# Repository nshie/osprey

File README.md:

# Osprey
A unibody ergonomic ortholinear keyboard
- ergonomic wrist angle
- ortholinear columnar-stagger
- 60% layout (~ish)
- thumb clusters for modifiers and chording
- kailh hotswap sockets
- USB-C

### Features to change:
- leds in the pcb are not properly implemented with capacitors, WOULD NOT recommend building this board with the leds
- pcb uses 0805 diode pads; might have some difficulty finding them (0603 will work on the pcb)

## Important Note:
This board is very much a prototype, and I would not recommend using the files without modification.

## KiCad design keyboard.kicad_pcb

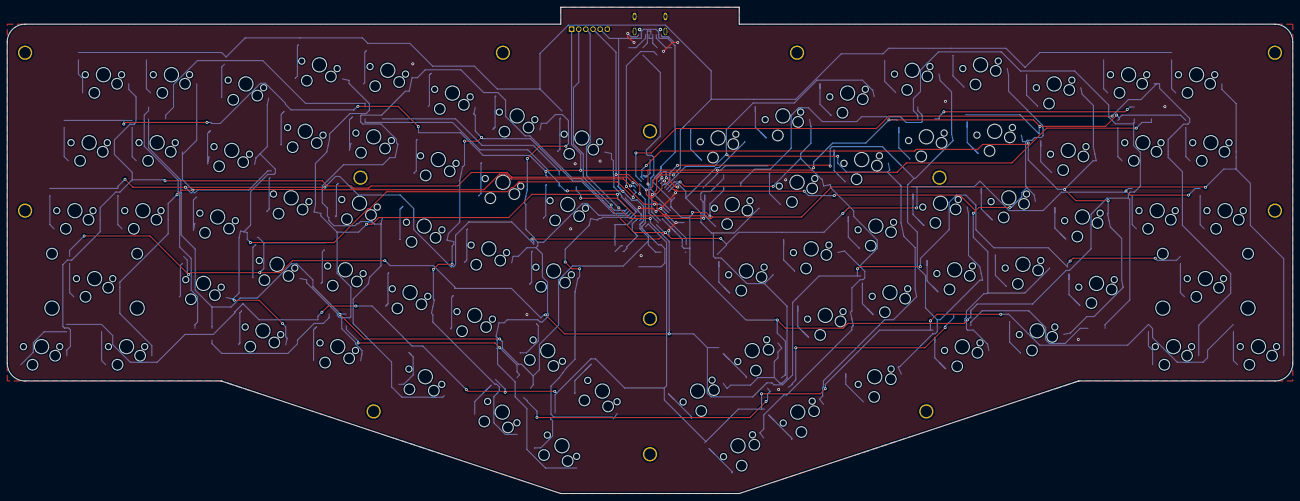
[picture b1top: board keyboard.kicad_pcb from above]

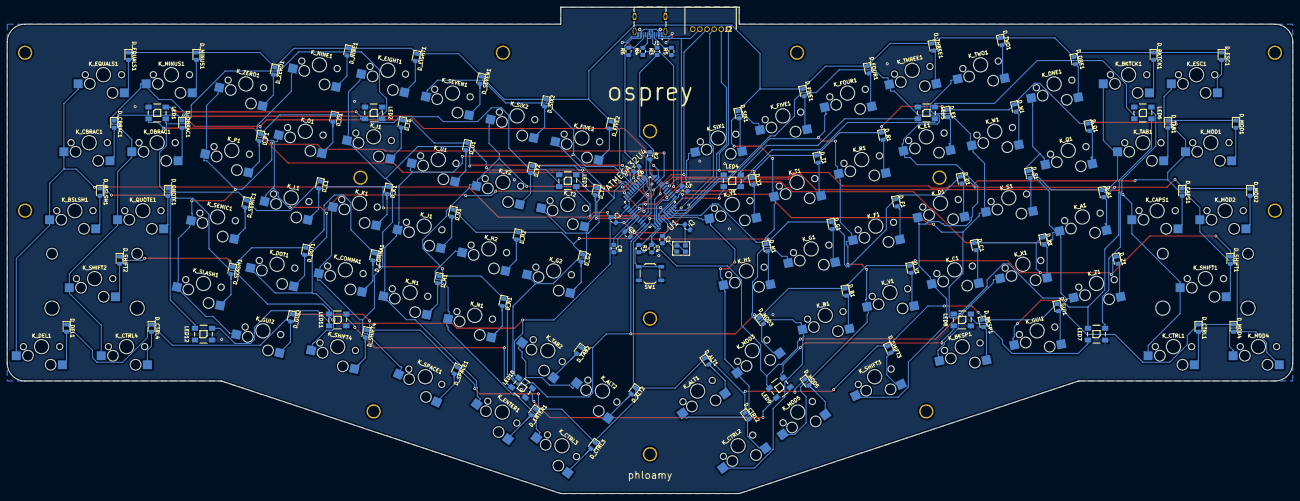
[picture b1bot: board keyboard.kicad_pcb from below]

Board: 2 copper layers, 360.2 x 136.3 mm, 200 parts (109 on the bottom side), 124 nets.

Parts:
C1, C2: 22p; C_0805_2012Metric_Pad1.15x1.40mm_HandSolder
C3, C4, C5, C6: 0.1u; C_0805_2012Metric_Pad1.15x1.40mm_HandSolder
C7: 4.7u; C_0805_2012Metric_Pad1.15x1.40mm_HandSolder
C8: 1u; C_0805_2012Metric_Pad1.15x1.40mm_HandSolder
D_A1: D; D_0805_2012Metric_Pad1.15x1.40mm_HandSolder
D_ALT1, D_ALT2: D; D_0805_2012Metric_Pad1.15x1.40mm_HandSolder
D_B1: D; D_0805_2012Metric_Pad1.15x1.40mm_HandSolder
D_BKSP1: D; D_0805_2012Metric_Pad1.15x1.40mm_HandSolder
D_BKTCK1: D; D_0805_2012Metric_Pad1.15x1.40mm_HandSolder
D_BSLSH1: D; D_0805_2012Metric_Pad1.15x1.40mm_HandSolder
D_C1: D; D_0805_2012Metric_Pad1.15x1.40mm_HandSolder
D_CAPS1: D; D_0805_2012Metric_Pad1.15x1.40mm_HandSolder
D_CBRAC1: D; D_0805_2012Metric_Pad1.15x1.40mm_HandSolder
D_COMMA1: D; D_0805_2012Metric_Pad1.15x1.40mm_HandSolder
D_CTRL1, D_CTRL2, D_CTRL3, D_CTRL4: D; D_0805_2012Metric_Pad1.15x1.40mm_HandSolder
D_D1: D; D_0805_2012Metric_Pad1.15x1.40mm_HandSolder
D_DEL1: D; D_0805_2012Metric_Pad1.15x1.40mm_HandSolder
D_DOT1: D; D_0805_2012Metric_Pad1.15x1.40mm_HandSolder
D_E1: D; D_0805_2012Metric_Pad1.15x1.40mm_HandSolder
D_EIGHT1: D; D_0805_2012Metric_Pad1.15x1.40mm_HandSolder
D_ENTER1: D; D_0805_2012Metric_Pad1.15x1.40mm_HandSolder
D_EQUALS1: D; D_0805_2012Metric_Pad1.15x1.40mm_HandSolder
D_ESC1: D; D_0805_2012Metric_Pad1.15x1.40mm_HandSolder
D_F1: D; D_0805_2012Metric_Pad1.15x1.40mm_HandSolder
D_FIVE1, D_FIVE2: D; D_0805_2012Metric_Pad1.15x1.40mm_HandSolder
D_FOUR1: D; D_0805_2012Metric_Pad1.15x1.40mm_HandSolder
D_G1, D_G2: D; D_0805_2012Metric_Pad1.15x1.40mm_HandSolder
D_GUI1, D_GUI2: D; D_0805_2012Metric_Pad1.15x1.40mm_HandSolder
D_H1, D_H2: D; D_0805_2012Metric_Pad1.15x1.40mm_HandSolder
D_I1: D; D_0805_2012Metric_Pad1.15x1.40mm_HandSolder
D_J1: D; D_0805_2012Metric_Pad1.15x1.40mm_HandSolder
D_K1: D; D_0805_2012Metric_Pad1.15x1.40mm_HandSolder
D_L1: D; D_0805_2012Metric_Pad1.15x1.40mm_HandSolder
D_M1: D; D_0805_2012Metric_Pad1.15x1.40mm_HandSolder
D_MINUS1: D; D_0805_2012Metric_Pad1.15x1.40mm_HandSolder
D_MOD1, D_MOD2, D_MOD3, D_MOD4, D_MOD5: D; D_0805_2012Metric_Pad1.15x1.40mm_HandSolder
D_N1: D; D_0805_2012Metric_Pad1.15x1.40mm_HandSolder
D_NINE1: D; D_0805_2012Metric_Pad1.15x1.40mm_HandSolder
D_O1: D; D_0805_2012Metric_Pad1.15x1.40mm_HandSolder
D_OBRAC1: D; D_0805_2012Metric_Pad1.15x1.40mm_HandSolder
D_ONE1: D; D_0805_2012Metric_Pad1.15x1.40mm_HandSolder
D_P1: D; D_0805_2012Metric_Pad1.15x1.40mm_HandSolder
D_Q1: D; D_0805_2012Metric_Pad1.15x1.40mm_HandSolder
D_QUOTE1: D; D_0805_2012Metric_Pad1.15x1.40mm_HandSolder
D_R1: D; D_0805_2012Metric_Pad1.15x1.40mm_HandSolder
D_S1: D; D_0805_2012Metric_Pad1.15x1.40mm_HandSolder
D_SEMIC1: D; D_0805_2012Metric_Pad1.15x1.40mm_HandSolder
D_SEVEN1: D; D_0805_2012Metric_Pad1.15x1.40mm_HandSolder
D_SHIFT1, D_SHIFT2, D_SHIFT3, D_SHIFT4: D; D_0805_2012Metric_Pad1.15x1.40mm_HandSolder
D_SIX1, D_SIX2: D; D_0805_2012Metric_Pad1.15x1.40mm_HandSolder
D_SLASH1: D; D_0805_2012Metric_Pad1.15x1.40mm_HandSolder
D_SPACE1: D; D_0805_2012Metric_Pad1.15x1.40mm_HandSolder
D_T1, D_T2: D; D_0805_2012Metric_Pad1.15x1.40mm_HandSolder
D_TAB1, D_TAB2: D; D_0805_2012Metric_Pad1.15x1.40mm_HandSolder
D_THREE1: D; D_0805_2012Metric_Pad1.15x1.40mm_HandSolder
D_TWO1: D; D_0805_2012Metric_Pad1.15x1.40mm_HandSolder
D_U1: D; D_0805_2012Metric_Pad1.15x1.40mm_HandSolder
D_V1: D; D_0805_2012Metric_Pad1.15x1.40mm_HandSolder
D_W1: D; D_0805_2012Metric_Pad1.15x1.40mm_HandSolder
D_X1: D; D_0805_2012Metric_Pad1.15x1.40mm_HandSolder
D_Y1, D_Y2: D; D_0805_2012Metric_Pad1.15x1.40mm_HandSolder
D_Z1: D; D_0805_2012Metric_Pad1.15x1.40mm_HandSolder
D_ZERO1: D; D_0805_2012Metric_Pad1.15x1.40mm_HandSolder
HOLE1, HOLE2, HOLE3, HOLE4, HOLE5, HOLE6, HOLE7, HOLE8, HOLE9, HOLE10, HOLE11, HOLE12, HOLE13: HOLE_M3
J1: TYPE-C-31-M-12; HRO_TYPE-C-31-M-12
J2: DF3A-6P-2DS; SHDRRA6W60P0X200_1X6_1400X720X530P
K_A1: KEYSW; MXOnly-1U-Hotswap
K_ALT1, K_ALT2: KEYSW; MXOnly-1U-Hotswap
K_B1: KEYSW; MXOnly-1U-Hotswap
K_BKSP1: KEYSW; MXOnly-1.25U-Hotswap
K_BKTCK1: KEYSW; MXOnly-1U-Hotswap
K_BSLSH1: KEYSW; MXOnly-1U-Hotswap
K_C1: KEYSW; MXOnly-1U-Hotswap
K_CAPS1: KEYSW; MXOnly-1U-Hotswap
K_CBRAC1: KEYSW; MXOnly-1U-Hotswap
K_COMMA1: KEYSW; MXOnly-1U-Hotswap
K_CTRL1, K_CTRL4: KEYSW; MXOnly-1.5U-Hotswap
K_CTRL2, K_CTRL3: KEYSW; MXOnly-1U-Hotswap
K_D1: KEYSW; MXOnly-1U-Hotswap
K_DEL1: KEYSW; MXOnly-1U-Hotswap
K_DOT1: KEYSW; MXOnly-1U-Hotswap
K_E1: KEYSW; MXOnly-1U-Hotswap
K_EIGHT1: KEYSW; MXOnly-1U-Hotswap
K_ENTER1: KEYSW; MXOnly-1U-Hotswap
K_EQUALS1: KEYSW; MXOnly-1U-Hotswap
K_ESC1: KEYSW; MXOnly-1U-Hotswap
K_F1: KEYSW; MXOnly-1U-Hotswap
K_FIVE1, K_FIVE2: KEYSW; MXOnly-1U-Hotswap
K_FOUR1: KEYSW; MXOnly-1U-Hotswap
K_G1, K_G2: KEYSW; MXOnly-1U-Hotswap
K_GUI1, K_GUI2: KEYSW; MXOnly-1U-Hotswap
K_H1, K_H2: KEYSW; MXOnly-1U-Hotswap
K_I1: KEYSW; MXOnly-1U-Hotswap
K_J1: KEYSW; MXOnly-1U-Hotswap
K_K1: KEYSW; MXOnly-1U-Hotswap
K_L1: KEYSW; MXOnly-1U-Hotswap
K_M1: KEYSW; MXOnly-1U-Hotswap
K_MINUS1: KEYSW; MXOnly-1U-Hotswap
K_MOD1, K_MOD2, K_MOD3, K_MOD4, K_MOD5: KEYSW; MXOnly-1U-Hotswap
K_N1: KEYSW; MXOnly-1U-Hotswap
K_NINE1: KEYSW; MXOnly-1U-Hotswap
K_O1: KEYSW; MXOnly-1U-Hotswap
K_OBRAC1: KEYSW; MXOnly-1U-Hotswap
K_ONE1: KEYSW; MXOnly-1U-Hotswap
K_P1: KEYSW; MXOnly-1U-Hotswap
K_Q1: KEYSW; MXOnly-1U-Hotswap
K_QUOTE1: KEYSW; MXOnly-1U-Hotswap
K_R1: KEYSW; MXOnly-1U-Hotswap
K_S1: KEYSW; MXOnly-1U-Hotswap
K_SEMIC1: KEYSW; MXOnly-1U-Hotswap
K_SEVEN1: KEYSW; MXOnly-1U-Hotswap
K_SHIFT1, K_SHIFT2: KEYSW; MXOnly-2U-Hotswap-ReversedStabilizers
K_SHIFT3, K_SHIFT4: KEYSW; MXOnly-1.25U-Hotswap
K_SIX1, K_SIX2: KEYSW; MXOnly-1U-Hotswap
K_SLASH1: KEYSW; MXOnly-1U-Hotswap
K_SPACE1: KEYSW; MXOnly-1.25U-Hotswap
K_T1, K_T2: KEYSW; MXOnly-1U-Hotswap
K_TAB1, K_TAB2: KEYSW; MXOnly-1U-Hotswap
K_THREE1: KEYSW; MXOnly-1U-Hotswap
K_TWO1: KEYSW; MXOnly-1U-Hotswap
K_U1: KEYSW; MXOnly-1U-Hotswap
K_V1: KEYSW; MXOnly-1U-Hotswap
K_W1: KEYSW; MXOnly-1U-Hotswap
K_X1: KEYSW; MXOnly-1U-Hotswap
K_Y1, K_Y2: KEYSW; MXOnly-1U-Hotswap
K_Z1: KEYSW; MXOnly-1U-Hotswap
K_ZERO1: KEYSW; MXOnly-1U-Hotswap
LED1, LED2, LED3, LED4, LED5, LED6, LED7, LED8, LED9, LED10, LED11, LED12: WS2812B
R1, R2: 10k; R_0805_2012Metric_Pad1.15x1.40mm_HandSolder
R3, R4: 22; R_0805_2012Metric_Pad1.15x1.40mm_HandSolder
R5, R6: 5.1k; R_0805_2012Metric_Pad1.15x1.40mm_HandSolder
SW1: SW_PUSH; SW_SPST_TL3342
U1: ATMEGA32U4; ATmega32U4
X1: XTAL_GND; FA-238

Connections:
GND: C1.2, C2.2, C3.2, C4.2, C5.2, C6.2, C7.2, C8.2, J1.A1B12, J1.B1A12, J1.S1, J1.S2, J1.S3, J1.S4, J2.6, LED1.3, LED2.3, LED3.3, LED4.3, LED5.3, LED6.3, LED7.3, LED8.3, LED9.3, LED10.3, LED11.3, LED12.3, R2.1, R5.1, R6.1, SW1.1, U1.5, U1.15, U1.23, U1.35, U1.43, X1.3
unnamed: C1.1, U1.16, X1.1
unnamed: C2.1, U1.17, X1.2
unnamed: C8.1, U1.6
unnamed: D_A1.2, K_A1.2
unnamed: D_ALT1.2, K_ALT1.2
unnamed: D_ALT2.2, K_ALT2.2
unnamed: D_B1.2, K_B1.2
unnamed: D_BKSP1.2, K_BKSP1.2
unnamed: D_BKTCK1.2, K_BKTCK1.2
unnamed: D_BSLSH1.2, K_BSLSH1.2
unnamed: D_C1.2, K_C1.2
unnamed: D_CAPS1.2, K_CAPS1.2
unnamed: D_CBRAC1.2, K_CBRAC1.2
unnamed: D_COMMA1.2, K_COMMA1.2
unnamed: D_CTRL1.2, K_CTRL1.2
unnamed: D_CTRL2.2, K_CTRL2.2
unnamed: D_CTRL3.2, K_CTRL3.2
unnamed: D_CTRL4.2, K_CTRL4.2
unnamed: D_D1.2, K_D1.2
unnamed: D_DEL1.2, K_DEL1.2
unnamed: D_DOT1.2, K_DOT1.2
unnamed: D_E1.2, K_E1.2
unnamed: D_EIGHT1.2, K_EIGHT1.2
unnamed: D_ENTER1.2, K_ENTER1.2
unnamed: D_EQUALS1.2, K_EQUALS1.2
unnamed: D_ESC1.2, K_ESC1.2
unnamed: D_F1.2, K_F1.2
unnamed: D_FIVE1.2, K_FIVE1.2
unnamed: D_FIVE2.2, K_FIVE2.2
unnamed: D_FOUR1.2, K_FOUR1.2
unnamed: D_G1.2, K_G1.2
unnamed: D_G2.2, K_G2.2
unnamed: D_GUI1.2, K_GUI1.2
unnamed: D_GUI2.2, K_GUI2.2
unnamed: D_H1.2, K_H1.2
unnamed: D_H2.2, K_H2.2
unnamed: D_I1.2, K_I1.2
unnamed: D_J1.2, K_J1.2
unnamed: D_K1.2, K_K1.2
unnamed: D_L1.2, K_L1.2
unnamed: D_M1.2, K_M1.2
unnamed: D_MINUS1.2, K_MINUS1.2
unnamed: D_MOD1.2, K_MOD1.2
unnamed: D_MOD2.2, K_MOD2.2
unnamed: D_MOD3.2, K_MOD3.2
unnamed: D_MOD4.2, K_MOD4.2
unnamed: D_MOD5.2, K_MOD5.2
unnamed: D_N1.2, K_N1.2
unnamed: D_NINE1.2, K_NINE1.2
unnamed: D_O1.2, K_O1.2
unnamed: D_OBRAC1.2, K_OBRAC1.2
unnamed: D_ONE1.2, K_ONE1.2
unnamed: D_P1.2, K_P1.2
unnamed: D_Q1.2, K_Q1.2
unnamed: D_QUOTE1.2, K_QUOTE1.2
unnamed: D_R1.2, K_R1.2
unnamed: D_S1.2, K_S1.2
unnamed: D_SEMIC1.2, K_SEMIC1.2
unnamed: D_SEVEN1.2, K_SEVEN1.2
unnamed: D_SHIFT1.2, K_SHIFT1.2
unnamed: D_SHIFT2.2, K_SHIFT2.2
unnamed: D_SHIFT3.2, K_SHIFT3.2
unnamed: D_SHIFT4.2, K_SHIFT4.2
unnamed: D_SIX1.2, K_SIX1.2
unnamed: D_SIX2.2, K_SIX2.2
unnamed: D_SLASH1.2, K_SLASH1.2
unnamed: D_SPACE1.2, K_SPACE1.2
unnamed: D_T1.2, K_T1.2
unnamed: D_T2.2, K_T2.2
unnamed: D_TAB1.2, K_TAB1.2
unnamed: D_TAB2.2, K_TAB2.2
unnamed: D_THREE1.2, K_THREE1.2
unnamed: D_TWO1.2, K_TWO1.2
unnamed: D_U1.2, K_U1.2
unnamed: D_V1.2, K_V1.2
unnamed: D_W1.2, K_W1.2
unnamed: D_X1.2, K_X1.2
unnamed: D_Y1.2, K_Y1.2
unnamed: D_Y2.2, K_Y2.2
unnamed: D_Z1.2, K_Z1.2
unnamed: D_ZERO1.2, K_ZERO1.2
unnamed: J1.A5, R5.2
unnamed: J1.A6, J1.B6, R4.2
unnamed: J1.A7, J1.B7, R3.2
unnamed: J1.B5, R6.2
unnamed: LED1.2, LED2.4
unnamed: LED2.2, LED3.4
unnamed: LED3.2, LED4.4
unnamed: LED4.2, LED5.4
unnamed: LED5.2, LED6.4
unnamed: LED6.2, LED7.4
unnamed: LED7.2, LED8.4
unnamed: LED8.2, LED9.4
unnamed: LED10.2, LED11.4
unnamed: LED9.2, LED10.4
unnamed: LED11.2, LED12.4
unnamed: R2.2, U1.33
unnamed: R3.1, U1.3
unnamed: R4.1, U1.4
VCC: C3.1, C4.1, C5.1, C6.1, C7.1, J1.A4B9, J1.B4A9, J2.5, LED1.1, LED2.1, LED3.1, LED4.1, LED5.1, LED6.1, LED7.1, LED8.1, LED9.1, LED10.1, LED11.1, LED12.1, R1.2, U1.2, U1.7, U1.14, U1.24, U1.34, U1.44
col0: K_ESC1.1, K_MOD1.1, K_MOD2.1, K_MOD4.1, U1.29
col1: K_BKTCK1.1, K_CAPS1.1, K_CTRL1.1, K_SHIFT1.1, K_TAB1.1, U1.28
col2: K_A1.1, K_GUI1.1, K_ONE1.1, K_Q1.1, K_Z1.1, U1.27
col3: K_BKSP1.1, K_S1.1, K_TWO1.1, K_W1.1, K_X1.1, U1.22
col4: K_C1.1, K_D1.1, K_E1.1, K_SHIFT3.1, K_THREE1.1, U1.21
col5: K_F1.1, K_FOUR1.1, K_MOD5.1, K_R1.1, K_V1.1, U1.20
col6: K_B1.1, K_CTRL2.1, K_FIVE1.1, K_G1.1, K_T1.1, U1.19
col7: K_ALT1.1, K_H1.1, K_MOD3.1, K_SIX1.1, K_Y1.1, U1.18
col8: K_ALT2.1, K_FIVE2.1, K_G2.1, K_T2.1, K_TAB2.1, U1.41
col9: K_CTRL3.1, K_H2.1, K_N1.1, K_SIX2.1, K_Y2.1, U1.40
col10: K_ENTER1.1, K_J1.1, K_M1.1, K_SEVEN1.1, K_U1.1, U1.39
col11: K_COMMA1.1, K_EIGHT1.1, K_I1.1, K_K1.1, K_SPACE1.1, U1.38
col12: K_DOT1.1, K_L1.1, K_NINE1.1, K_O1.1, K_SHIFT4.1, U1.37
col13: K_GUI2.1, K_P1.1, K_SEMIC1.1, K_SLASH1.1, K_ZERO1.1, U1.32
col14: K_CTRL4.1, K_MINUS1.1, K_OBRAC1.1, K_QUOTE1.1, K_SHIFT2.1, U1.31
col15: K_BSLSH1.1, K_CBRAC1.1, K_DEL1.1, K_EQUALS1.1, U1.30
led: LED1.4, U1.36
reset: J2.4, R1.1, SW1.2, U1.13
row0: D_BKTCK1.1, D_EIGHT1.1, D_EQUALS1.1, D_ESC1.1, D_FIVE1.1, D_FIVE2.1, D_FOUR1.1, D_MINUS1.1, D_NINE1.1, D_ONE1.1, D_SEVEN1.1, D_SIX1.1, D_SIX2.1, D_THREE1.1, D_TWO1.1, D_ZERO1.1, U1.8
row1: D_CBRAC1.1, D_E1.1, D_I1.1, D_MOD1.1, D_O1.1, D_OBRAC1.1, D_P1.1, D_Q1.1, D_R1.1, D_T1.1, D_T2.1, D_TAB1.1, D_U1.1, D_W1.1, D_Y1.1, D_Y2.1, J2.1, U1.9
row2: D_A1.1, D_BSLSH1.1, D_CAPS1.1, D_D1.1, D_F1.1, D_G1.1, D_G2.1, D_H1.1, D_H2.1, D_J1.1, D_K1.1, D_L1.1, D_MOD2.1, D_QUOTE1.1, D_S1.1, D_SEMIC1.1, J2.2, U1.10
row3: D_B1.1, D_C1.1, D_COMMA1.1, D_DOT1.1, D_M1.1, D_MOD3.1, D_N1.1, D_SHIFT1.1, D_SHIFT2.1, D_SLASH1.1, D_TAB2.1, D_V1.1, D_X1.1, D_Z1.1, J2.3, U1.11
row4: D_ALT1.1, D_ALT2.1, D_BKSP1.1, D_CTRL1.1, D_CTRL2.1, D_CTRL3.1, D_CTRL4.1, D_DEL1.1, D_ENTER1.1, D_GUI1.1, D_GUI2.1, D_MOD4.1, D_MOD5.1, D_SHIFT3.1, D_SHIFT4.1, D_SPACE1.1, U1.12

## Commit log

2021-09-03 Rename keyboard-layout.json to kle/keyboard-layout.json
2021-09-03 Rename keyboard.sch to kicad/keyboard.sch
2021-09-03 Rename nonsplit-ergo-case-bottom-plate-2d.dxf to case/nonsplit-ergo-case-bottom-plate-2d.dxf
2021-09-03 Rename nonsplit-ergo-case-top-plate-2d.dxf to case/top-plate
2021-09-03 Rename nonsplit-ergo-case-bottom-plate-2d.dxf to bottom-plate.dxf
2021-09-03 Rename top-plate to top-plate.dxf
2021-09-03 Rename change-log.txt to layout-change-log.txt
2021-09-03 Rename layout-change-log.txt to kle/layout-change-log.txt
2021-09-03 Create f
2024-02-19 Added QMK config
